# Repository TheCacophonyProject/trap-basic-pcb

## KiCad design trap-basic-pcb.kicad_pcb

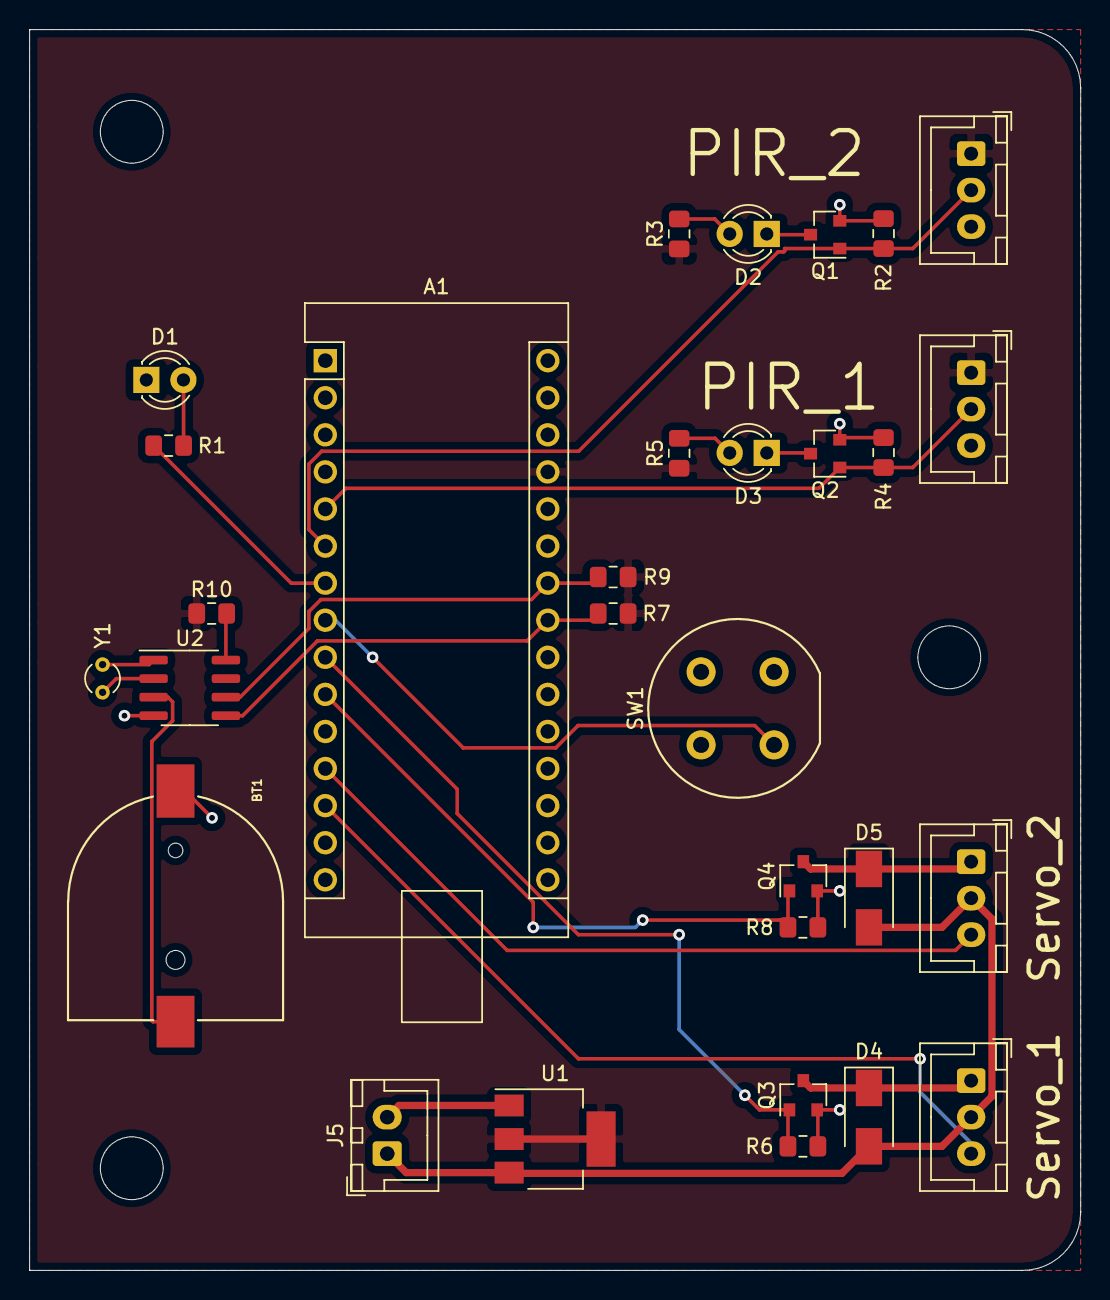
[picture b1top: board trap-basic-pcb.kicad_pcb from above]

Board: 2 copper layers, 72.0 x 85.0 mm, 33 parts (0 on the bottom side), 24 nets.

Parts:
A1: Arduino_Nano_v3.x; Arduino_Nano
BT1: Battery_Cell; CR1220
D1: STATUS_LED; LED_D3.0mm
D2: PIR_2_LED; LED_D3.0mm
D3: PIR_1_LED; LED_D3.0mm
D4, D5: D; D_SMA
H1, H2, H3: MountingHole; MountingHole_4.3mm_M4
J1: PIR_1; JST_XH_B3B-XH-A_1x03_P2.50mm_Vertical
J2: PIR_2; JST_XH_B3B-XH-A_1x03_P2.50mm_Vertical
J3: Servo_1; JST_XH_B3B-XH-A_1x03_P2.50mm_Vertical
J4: Servo_2; JST_XH_B3B-XH-A_1x03_P2.50mm_Vertical
J5: Conn_01x02; JST_XH_B2B-XH-A_1x02_P2.50mm_Vertical
Q1, Q2, Q3, Q4: Q_NMOS_GSD; SOT-23
R1, R3, R5: 470R; R_0805_2012Metric_Pad1.15x1.40mm_HandSolder
R2, R4, R6, R7, R8, R9: 10K; R_0805_2012Metric_Pad1.15x1.40mm_HandSolder
R10: 1K; R_0805_2012Metric_Pad1.15x1.40mm_HandSolder
SW1: SW_DIP_x01; Push_E-Switch_KS01Q01
U1: AMS1117-5.0; SOT-223-3_TabPin2
U2: PCF8523T; SOIC-8_3.9x4.9mm_P1.27mm
Y1: Crystal; Crystal_DS26_D2.0mm_L6.0mm_Vertical

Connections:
+5V: A1.27, J1.1, J2.1, R3.1, R5.1, R7.1, R9.1, R10.1, U1.2
/Man_Trigger: A1.8, SW1.3
/PIR_1: A1.5, J1.2, Q2.1, R4.1
/PIR_2: A1.6, J2.2, Q1.1, R2.1
/SCL: A1.24, R9.2, U2.6
/SDA: A1.23, R7.2, U2.5
/Servo_1: A1.13, J3.3
/Servo_1_P: A1.9, Q3.1, R6.1
/Servo_2: A1.12, J4.3
/Servo_2_P: A1.10, Q4.1, R8.1
/Status_LED: A1.7, R1.1
GND: A1.4, A1.29, BT1.2, D1.1, J1.3, J2.3, J5.2, Q1.2, Q2.2, Q3.2, Q4.2, R2.2, R4.2, R6.2, R8.2, SW1.2, U1.1, U2.4
unnamed: BT1.1, U2.3
unnamed: D1.2, R1.2
unnamed: D2.1, Q1.3
unnamed: D2.2, R3.2
unnamed: D3.1, Q2.3
unnamed: D3.2, R5.2
unnamed: D4.1, J3.1, Q3.3
unnamed: D5.1, J4.1, Q4.3
unnamed: R10.2, U2.8
unnamed: U2.1, Y1.1
unnamed: U2.2, Y1.2
VCC: D4.2, D5.2, J3.2, J4.2, J5.1, U1.3

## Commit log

2020-09-11 Add .gitignore
2020-09-11 Add fabrication output folder
2020-09-11 version 0.1.0
